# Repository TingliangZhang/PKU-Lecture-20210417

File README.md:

# PKU-Lecture-20210417
20210417北大课程大纲

以NFC Tag为例的硬件综述讲座

介绍NFC原理和应用，和大家一起设计一款电子名片，并走完PCB设计从电路原理到布线生产的全流程，作为入门硬件的引子。

近距离无线通信（Near-field communication，NFC）是一套通信协议，让两个电子设备（其中一个通常是移动设备，例如智能手机）在相距几厘米之内进行通信。广泛应用于移动支付、身份证、钥匙卡等领域。

PCB（ Printed Circuit Board）是电子元件的支撑体，现代很多电子设备中都有PCB。

元培×极客创意动手实践课

模块二 课程主题二: AI艺术图像迁移及近场通讯展示.

https://mp.weixin.qq.com/s/RXo18wlO2YcmIqOoUKuKgA

## 涵盖的领域

电路相关

NFC射频技术

PCB相关

## Outline

NFC技术介绍

PCB和电路相关知识

如何设计PCB

交付打样

焊接

界面设计

服务器搭建

## 参考PPT

PCB培训PPT

## Timeline

Datasheet阅读

原理图设计

元件选型和采购，封装确认

绘制天线

PCB Layout设计

交付打样的流程

## 用得到的网页链接

https://eds.st.com/antenna/

https://www.bilibili.com/video/BV1pf4y1v7RL

## 一些计算

电路中天线电感计算计算：

主要参考AN2866 -  Antenna design procedure

Internal tuning capacitor in ST25DV04K SO8N(f = 13.56 MHz) $C_{TUN} = 28.5 pF$

计算公式：
$$
L_{A} C_{S} \omega^{2}=1
$$
具体推导：
$$
L_{A}=\frac{1}{4 \pi^{2} f^{2} C_{S}}
$$

$$
L_{A}=\frac{1}{4*3.14^{2}*13.56^{2}*28.5}=4.84uH
$$

## 用得到的参数

嘉立创PCB成品外层铜厚1oz~2oz(35um~70um)选择35um

单片出货，走线和焊盘距板边距离≥0.2mm，否则可能涉及到板内的线路及焊盘。

直接留3.18mm边缘。

最小线隙，多层板3.5mil 单双面板5mil (1mil=1/1000inch=0.0254mm)

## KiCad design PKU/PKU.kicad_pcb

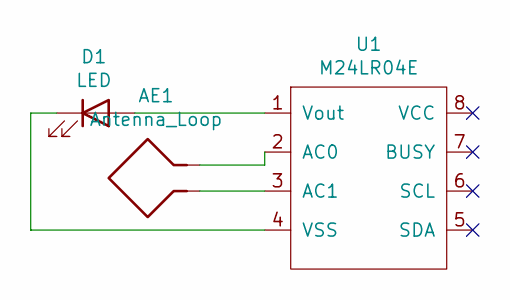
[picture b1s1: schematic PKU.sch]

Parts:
AE1: Antenna_Loop; NFC-Antenna_6_80.0x45.0_0.6x0.6mm
D1: LED; LED_0603_1608Metric_Castellated
U1: M24LR04E; SO-8_3.9x4.9mm_P1.27mm

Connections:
unnamed: AE1.1, U1.3 (AC1)
unnamed: AE1.2, U1.2 (AC0)
unnamed: D1.1 (K), U1.4 (VSS)
unnamed: D1.2 (A), U1.1 (Vout)

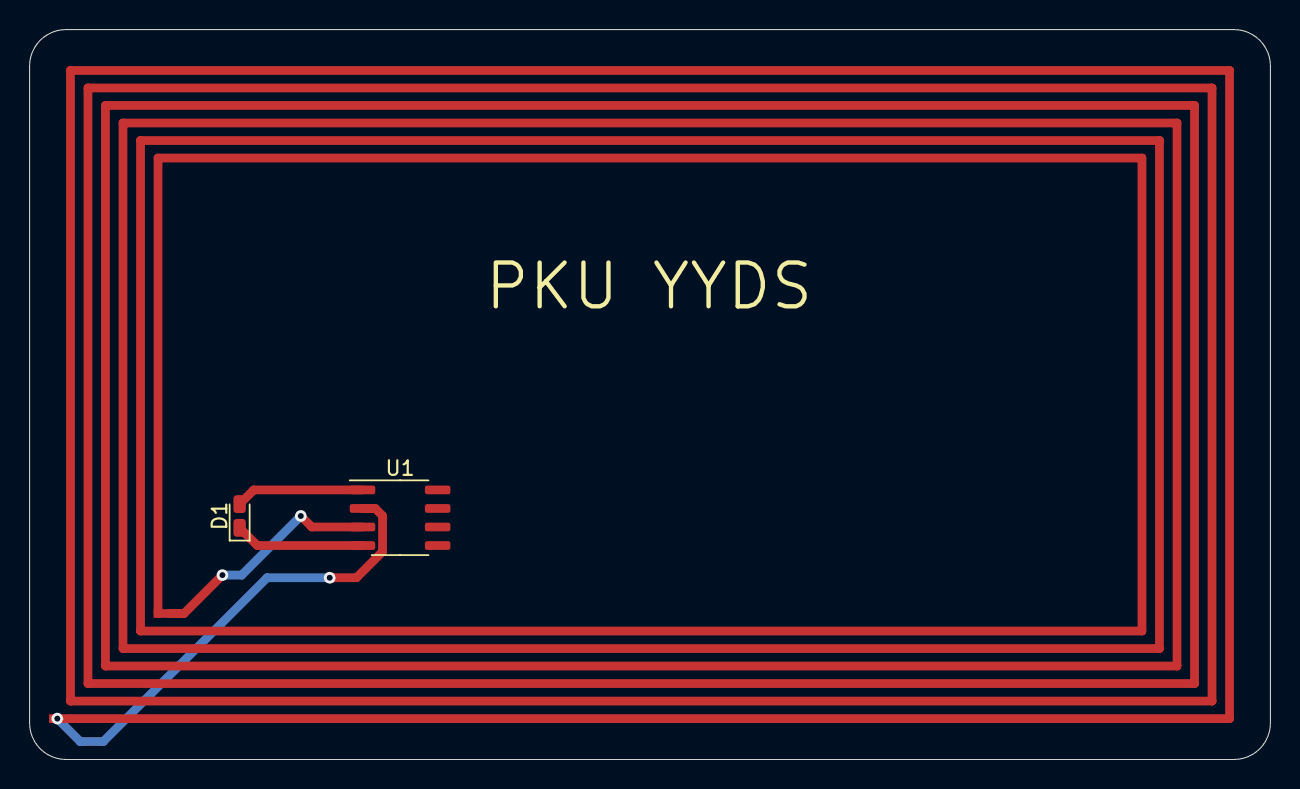
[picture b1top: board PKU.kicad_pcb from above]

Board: 2 copper layers, 85.0 x 50.0 mm, 3 parts (0 on the bottom side), 4 nets.

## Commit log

2021-05-21 finish
